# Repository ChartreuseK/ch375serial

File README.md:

# CH375 to RS-232 Adapter

This adapter is designed to allow usb mass storage media to be accessible to a computer over standard RS232. As such it contains a CH375 to do the heavy lifting along with a MAX3232 rs-232 level shifter to drive full serial levels. An external regulated 5v source is required to power the device as well as any attached USB storage devices. This could be provided by a USB to barrel jack adapter with a cell phone charger, a stand alone switching wall supply, or possibly even by a ps/2 keyboard port tap that borrows some power from such a port.

This is still in the testing stage and has not yet been constructed, however the circuitry is heavilly based on the original datasheet examples so likely will work.

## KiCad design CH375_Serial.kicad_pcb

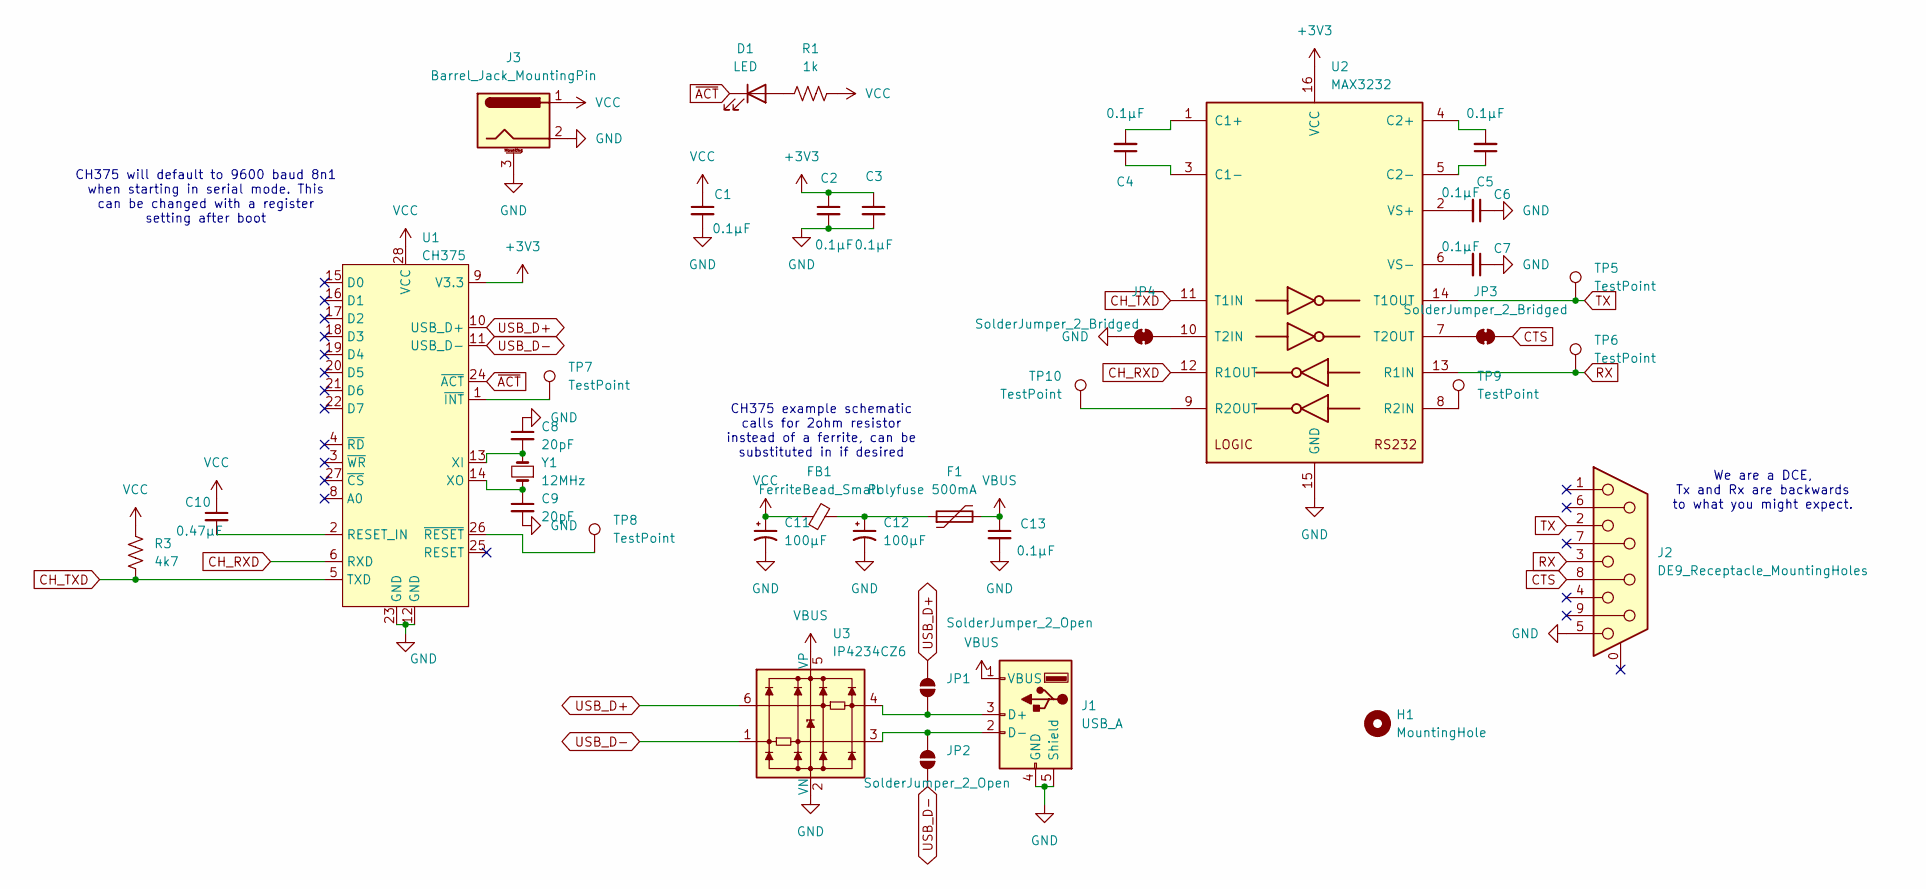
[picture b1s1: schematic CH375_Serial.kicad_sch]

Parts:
C1, C2, C3, C4, C5, C6, C7, C13: 0.1µF; C_0805_2012Metric_Pad1.18x1.45mm_HandSolder
C8, C9: 20pF; C_0805_2012Metric_Pad1.18x1.45mm_HandSolder
C10: 0.47µF; C_0805_2012Metric_Pad1.18x1.45mm_HandSolder
C11, C12: 100µF; CP_Elec_6.3x5.9
D1: LED; LED_D3.0mm
F1: Polyfuse 500mA; R_0805_2012Metric_Pad1.20x1.40mm_HandSolder
FB1: FerriteBead_Small; L_0805_2012Metric_Pad1.15x1.40mm_HandSolder
H1: MountingHole; MountingHole_2.2mm_M2
J1: USB_A; USB_A_Molex_67643_Horizontal
J2: DE9_Receptacle_MountingHoles; DSUB-9_Female_Horizontal_P2.77x2.84mm_EdgePinOffset7.70mm_H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
J3: Barrel_Jack_MountingPin; BarrelJack_Horizontal
JP1, JP2: SolderJumper_2_Open; SolderJumper-2_P1.3mm_Open_RoundedPad1.0x1.5mm
JP3, JP4: SolderJumper_2_Bridged; SolderJumper-2_P1.3mm_Bridged_RoundedPad1.0x1.5mm
R1: 1k; R_0805_2012Metric_Pad1.20x1.40mm_HandSolder
R3: 4k7; R_0805_2012Metric_Pad1.20x1.40mm_HandSolder
TP5, TP6, TP7, TP8, TP9, TP10: TestPoint; TestPoint_Pad_D1.0mm
U1: CH375; SOP-28_8.4x18.16mm_P1.27mm
U2: MAX3232; SOIC-16_3.9x9.9mm_P1.27mm
U3: IP4234CZ6; SC-74-6_1.55x2.9mm_P0.95mm
Y1: 12MHz; Crystal_HC49-4H_Vertical

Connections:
+3V3: C2.1, C3.1, U1.9 (V3.3), U2.16 (VCC)
CH_RXD: U1.6 (RXD), U2.12 (R1OUT)
CH_TXD: R3.1, U1.5 (TXD), U2.11 (T1IN)
CTS: J2.8, JP3.2 (B)
GND: C1.2, C2.2, C3.2, C6.1, C7.1, C8.1, C9.2, C11.2, C12.2, C13.2, J1.4 (GND), J1.5 (Shield), J2.5, J3.2, J3.3 (MountPin), JP4.1 (A), U1.12 (GND), U1.23 (GND), U2.15 (GND), U3.2 (VN)
unnamed: C12.1, F1.1, FB1.2
unnamed: D1.2 (A), R1.1
unnamed: J1.3 (D+), JP1.1 (A), U3.4
unnamed: J1.2 (D-), JP2.2 (B), U3.3
unnamed: JP3.1 (A), U2.7 (T2OUT)
unnamed: JP4.2 (B), U2.10 (T2IN)
unnamed: C10.2, U1.2 (RESET_IN)
unnamed: C8.2, U1.13 (XI), Y1.2
unnamed: C9.1, U1.14 (XO), Y1.1
unnamed: TP7.1, U1.1 (~INT)
unnamed: TP8.1, U1.26 (~RESET)
unnamed: C4.2, U2.1 (C1+)
unnamed: C4.1, U2.3 (C1-)
unnamed: C5.2, U2.4 (C2+)
unnamed: C5.1, U2.5 (C2-)
unnamed: TP9.1, U2.8 (R2IN)
unnamed: TP10.1, U2.9 (R2OUT)
unnamed: C6.2, U2.2 (VS+)
unnamed: C7.2, U2.6 (VS-)
RX: J2.3, TP6.1, U2.13 (R1IN)
TX: J2.2, TP5.1, U2.14 (T1OUT)
USB_D+: JP1.2 (B), U1.10 (USB_D+), U3.6
USB_D-: JP2.1 (A), U1.11 (USB_D-), U3.1
VBUS: C13.1, F1.2, J1.1 (VBUS), U3.5 (VP)
VCC: C1.1, C10.1, C11.1, FB1.1, J3.1, R1.2, R3.2, U1.28 (VCC)
~ACT: D1.1 (K), U1.24 (~ACT)

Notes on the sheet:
CH375 example schematic calls for 2ohm resistor instead of a ferrite, can be substituted in if desired
CH375 will default to 9600 baud 8n1 when starting in serial mode. This can be changed with a register setting after boot
We are a DCE, Tx and Rx are backwards to what you might expect.

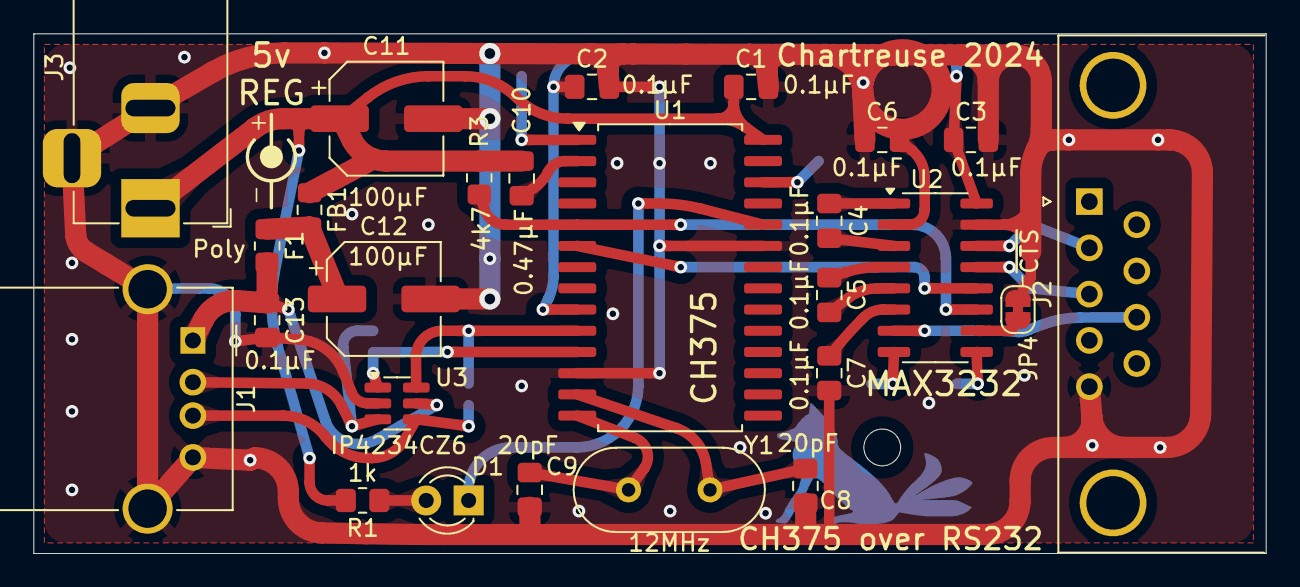
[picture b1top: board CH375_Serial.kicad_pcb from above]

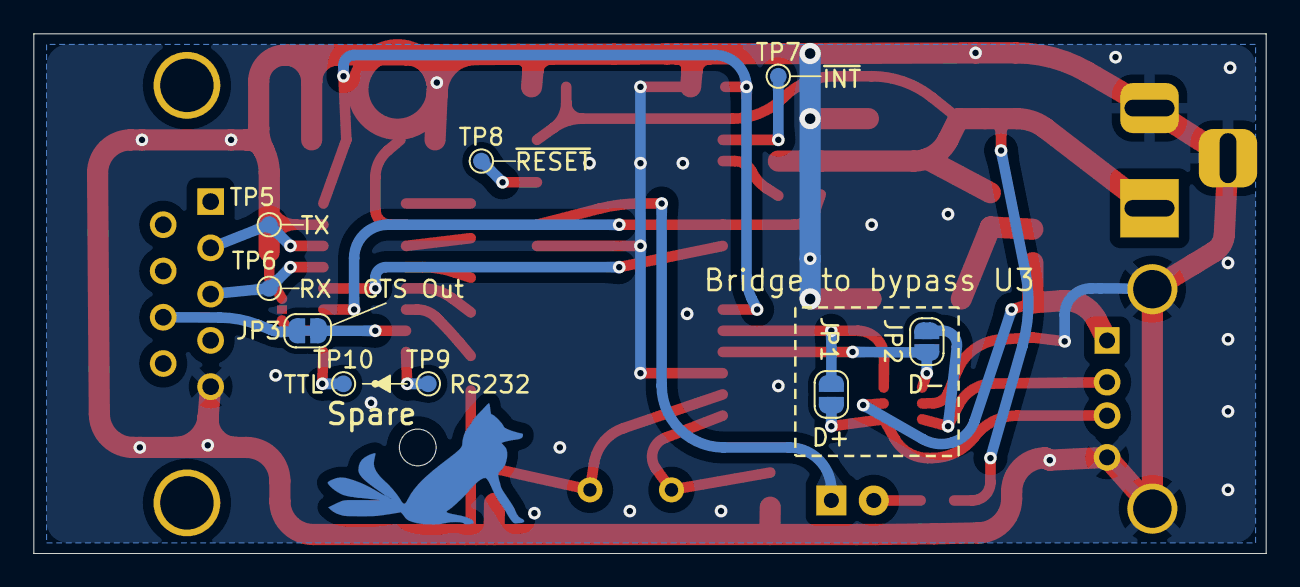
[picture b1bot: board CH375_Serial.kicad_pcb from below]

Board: 2 copper layers, 73.8 x 31.1 mm, 36 parts (9 on the bottom side), 31 nets.

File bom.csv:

Reference,Value,Datasheet,Footprint,Qty,DNP,LCSC
"C1,C2,C3,C4,C5,C6,C7,C13",0.1µF,~,Capacitor_SMD:C_0805_2012Metric_Pad1.18x1.45mm_HandSolder,8,,C49678
"C8,C9",20pF,~,Capacitor_SMD:C_0805_2012Metric_Pad1.18x1.45mm_HandSolder,2,,C1798
C10,0.47µF,~,Capacitor_SMD:C_0805_2012Metric_Pad1.18x1.45mm_HandSolder,1,,C13967
"C11,C12",100µF  16v,~,Capacitor_SMD:CP_Elec_6.3x5.9,2,,C340733
FB1,FerriteBead_Small,~,Inductor_SMD:L_0805_2012Metric_Pad1.15x1.40mm_HandSolder,1,,C1015
J1,USB_A,~,Connector_USB:USB_A_Molex_67643_Horizontal,1,,C456018
J2,DE9_Receptacle_MountingHoles,~,Connector_Dsub:DSUB-9_Female_Horizontal_P2.77x2.84mm_EdgePinOffset7.70mm_Housed_MountingHolesOffset9.12mm,1,,C19077337
J3,Barrel_Jack_MountingPin,~,Connector_BarrelJack:BarrelJack_Horizontal,1,,C16214
R1,1k,~,Resistor_SMD:R_0805_2012Metric_Pad1.20x1.40mm_HandSolder,1,,C17513
R3,4k7,~,Resistor_SMD:R_0805_2012Metric_Pad1.20x1.40mm_HandSolder,1,,C17673
U1,CH375,https://www.wch-ic.com/downloads/CH375DS1_PDF.html,Package_SO:SOP-28_8.4x18.16mm_P1.27mm,1,,C8962
U2,MAX3232,https://datasheets.maximintegrated.com/en/ds/MAX3222-MAX3241.pdf,Package_SO:SOIC-16_3.9x9.9mm_P1.27mm,1,,C193666
U3,IP4234CZ6,https://assets.nexperia.com/documents/data-sheet/IP4234CZ6.pdf,Package_TO_SOT_SMD:SC-74-6_1.55x2.9mm_P0.95mm,1,,C355086
Y1,12MHz,~,Crystal:Crystal_HC49-4H_Vertical,1,,C2857630

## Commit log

2024-07-17 Initial version of CH375 adapter.
2024-07-17 Added CERN-OHL-W license and initial readme.
2024-07-17 Added 3d render to readme
2024-07-17 Added LCSC part numbers for most, exported simple BOM
